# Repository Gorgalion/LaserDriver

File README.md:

# LaserDriver
MCU and current controller to drive laser.

Allign compoenents

Makes them compact

Assign 3d footprint to inductor and proper footprint to other compoennts

use 4 pin terminal

move arduino and other 3d files to project

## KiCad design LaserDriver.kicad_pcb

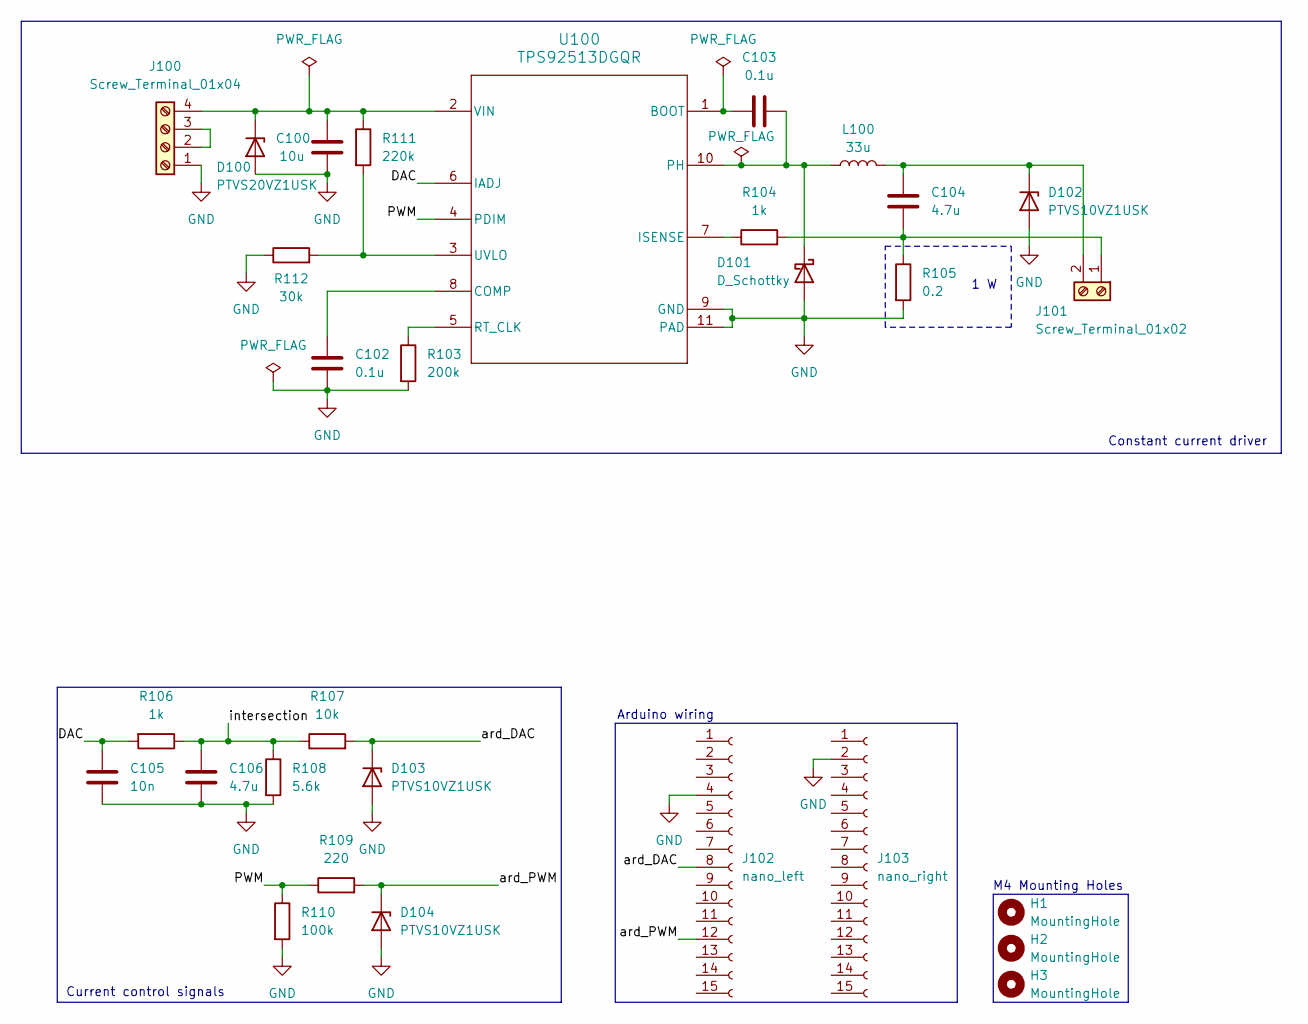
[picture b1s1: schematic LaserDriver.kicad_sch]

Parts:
C100: 10u; C_1206_3216Metric; Manufacturer Part Number CL31A106KAHNNNE
C102, C103: 0.1u; C_0603_1608Metric; Manufacturer Part Number CL10B104KB8NNNC
C104, C106: 4.7u; C_0805_2012Metric; Manufacturer Part Number CL21A475KAQNNNE
C105: 10n; C_0603_1608Metric; Manufacturer Part Number C0805C103K8RACAUTO
D100: PTVS20VZ1USK; Nexperia_DSN1608-2_1.6x0.8mm; Manufacturer Part Number PTVS20VZ1USKYL
D101: D_Schottky; D_SMB; Manufacturer Part Number FLSM115JE3
D102, D103, D104: PTVS10VZ1USK; Nexperia_DSN1608-2_1.6x0.8mm; Manufacturer Part Number PTVS10VZ1USKYL
H1, H2, H3: MountingHole; MountingHole_4.3mm_M4
J100: Screw_Terminal_01x04; TerminalBlock_Xinya_XY308-2.54-4P_1x04_P2.54mm_Horizontal; Manufacturer Part Number DB125-2.54-4P-GN-S
J101: Screw_Terminal_01x02; TerminalBlock_Xinya_XY308-2.54-2P_1x02_P2.54mm_Horizontal; Manufacturer Part Number DB125-2.54-2P-GN-S
J102: nano_left; PinSocket_1x15_P2.54mm_Vertical; Manufacturer Part Number ZX-PM2.54-1-15PY
J103: nano_right; PinSocket_1x15_P2.54mm_Vertical; Manufacturer Part Number ZX-PM2.54-1-15PY
L100: 33u; L_Bourns_SRP7028A_7.3x6.6mm; Manufacturer Part Number SRP7028A-330M
R103: 200k; R_0603_1608Metric; Manufacturer Part Number RC0603FR-07200KL
R104, R106: 1k; R_0603_1608Metric; Manufacturer Part Number RC0603FR-071KL
R105: 0.2; R_2512_6332Metric; Manufacturer Part Number RLP25FEER200
R107: 10k; R_0603_1608Metric; Manufacturer Part Number RC0603FR-0710KL
R108: 5.6k; R_0603_1608Metric; Manufacturer Part Number RC0603FR-075K6L
R109: 220; R_0603_1608Metric; Manufacturer Part Number RC0603FR-07220RL
R110: 100k; R_0603_1608Metric; Manufacturer Part Number RC0603FR-07100KL
R111: 220k; R_0603_1608Metric; Manufacturer Part Number RC0603FR-07220KL
R112: 30k; R_0603_1608Metric; Manufacturer Part Number RC0603FR-0730KL
U100: TPS92513DGQR; DGQ0010D_NV_L; Manufacturer Part Number TPS92513DGQR

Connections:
/DAC: C105.1, R106.2, U100.6 (IADJ)
/PWM: R109.1, R110.1, U100.4 (PDIM)
/ard_DAC: D103.1 (K), J102.8, R107.2
/ard_PWM: D104.1 (K), J102.12, R109.2
/intersection: C106.1, R106.1, R107.1, R108.1
GND: C100.2, C102.2, C105.2, C106.2, D100.2 (A), D101.2 (A), D102.2 (A), D103.2 (A), D104.2 (A), J100.1, J102.4, J103.2, R103.2, R105.2, R108.2, R110.2, R112.1, U100.9 (GND), U100.11 (PAD)
unnamed: C100.1, D100.1 (K), J100.4, R111.1, U100.2 (VIN)
unnamed: C103.2, D101.1 (K), L100.1, U100.10 (PH)
unnamed: C104.1, D102.1 (K), J101.2, L100.2
unnamed: J100.2, J100.3
unnamed: C104.2, J101.1, R104.2, R105.1
unnamed: C103.1, U100.1 (BOOT)
unnamed: C102.1, U100.8 (COMP)
unnamed: R104.1, U100.7 (ISENSE)
unnamed: R103.1, U100.5 (RT_CLK)
unnamed: R111.2, R112.2, U100.3 (UVLO)

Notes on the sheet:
M4 Mounting Holes
1 W
Arduino wiring
Current control signals
Constant current driver

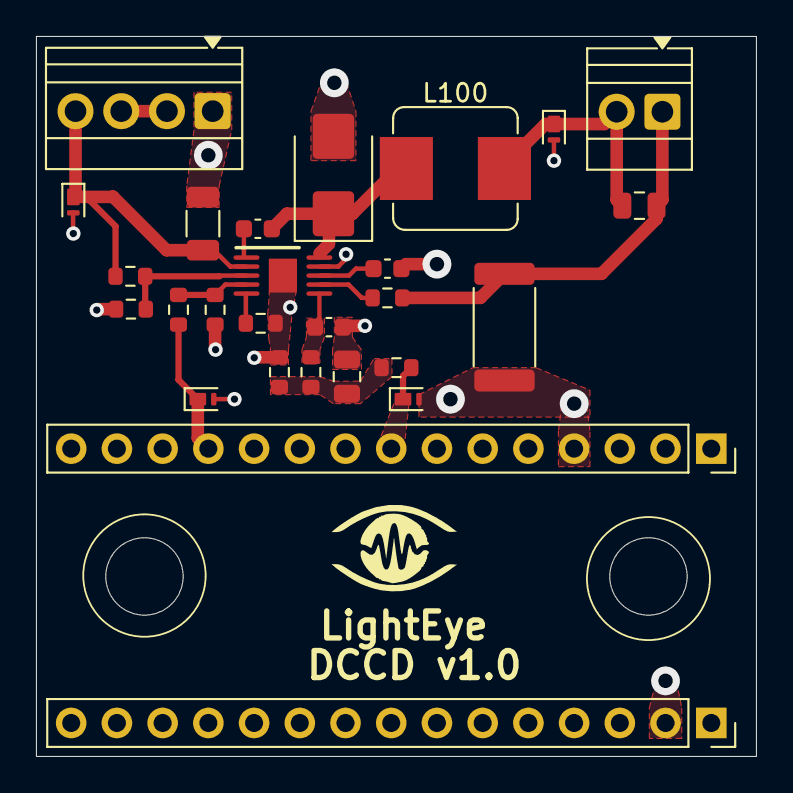
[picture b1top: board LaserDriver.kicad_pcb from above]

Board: 2 copper layers, 40.0 x 40.0 mm, 30 parts (0 on the bottom side), 16 nets.

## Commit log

2026-01-14 finished current control
2026-01-15 added arduino
2026-01-15 started footprints
2026-01-15 Started pcb editor
2026-01-20 added library
2026-01-20 add arduino 3d model
2026-01-21 added esd protection
2026-01-25 power changes
2026-01-25 added 3d models to project
2026-01-25 compactified design
2026-01-31 finihsed placing
2026-01-31 corrected arduino footprint
2026-01-31 Routing complete
2026-02-01 fixed errors
2026-02-01 added poors for ground
2026-02-01 added silkscreen and logo
2026-02-01 created calculator sheets
2026-02-02 created gerber and assembly files
2026-02-03 changes to tps ground via
2026-02-04 extended BOM
2026-02-05 finished BOM
2026-02-07 almost finishing
2026-04-02 increased screw size, fixed dimensions
2026-04-19 fine changes
2026-04-21 Fixed supplier and manufacturer issues
